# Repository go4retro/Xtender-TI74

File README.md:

# TI-74 Cartridge Port Extender

## Introduction

Basic port extender

## Requirements

- TI-74

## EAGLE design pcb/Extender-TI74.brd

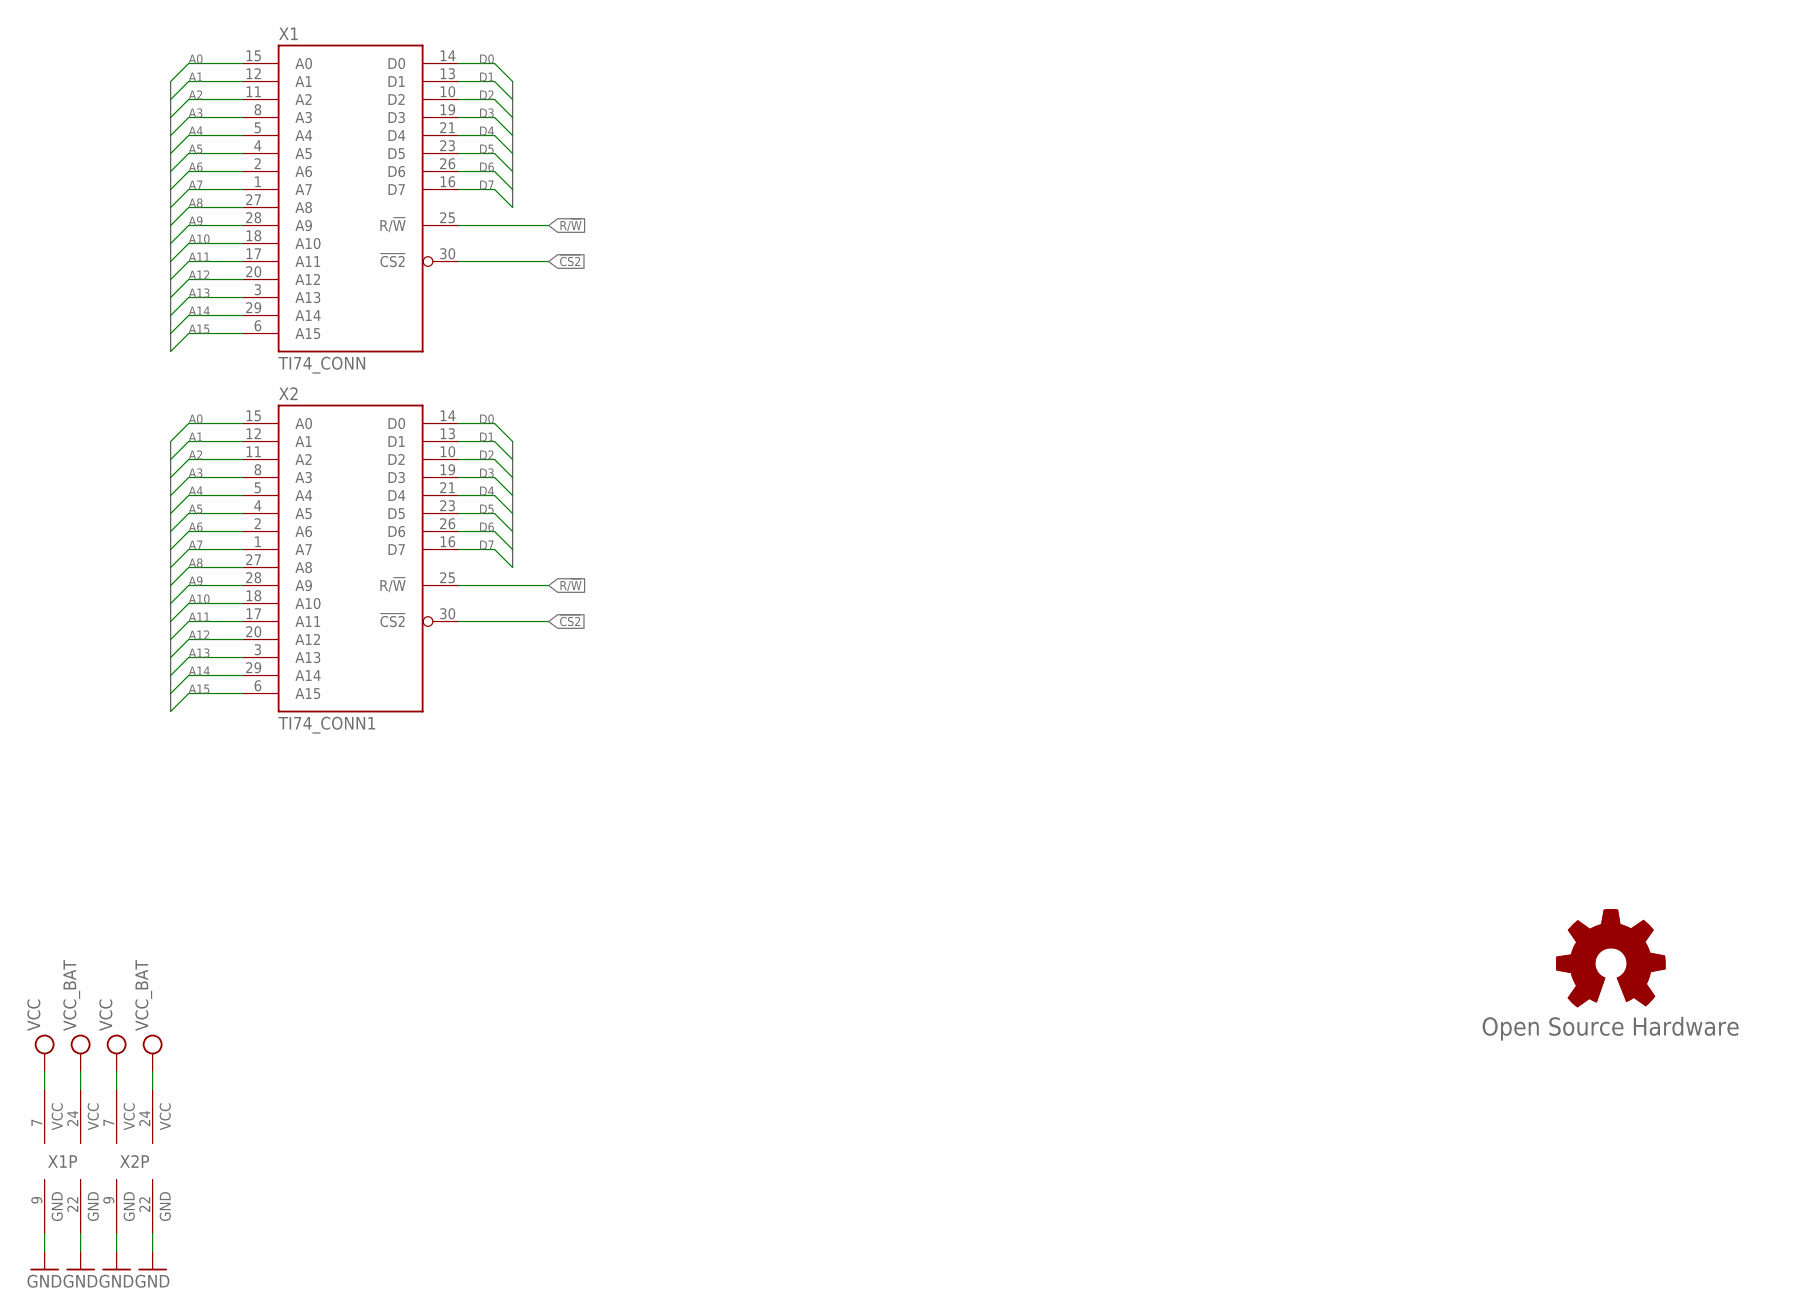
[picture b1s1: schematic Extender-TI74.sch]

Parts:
GOLD_ORB_SM1: Open Source Hardware; OSHW_5MM
X1: TI74_CONN; FE050-15-2SHORT
X2: TI74_CONN1; MA050-15-2

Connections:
!CS2: X1.30 (!CS2), X2.30 (!CS2)
A0: X1.15 (A0), X2.15 (A0)
A1: X1.12 (A1), X2.12 (A1)
A2: X1.11 (A2), X2.11 (A2)
A3: X1.8 (A3), X2.8 (A3)
A4: X1.5 (A4), X2.5 (A4)
A5: X1.4 (A5), X2.4 (A5)
A6: X1.2 (A6), X2.2 (A6)
A7: X1.1 (A7), X2.1 (A7)
A8: X1.27 (A8), X2.27 (A8)
A9: X1.28 (A9), X2.28 (A9)
A10: X1.18 (A10), X2.18 (A10)
A11: X1.17 (A11), X2.17 (A11)
A12: X1.20 (A12), X2.20 (A12)
A13: X1.3 (A13), X2.3 (A13)
A14: X1.29 (A14), X2.29 (A14)
A15: X1.6 (A15), X2.6 (A15)
D0: X1.14 (D0), X2.14 (D0)
D1: X1.13 (D1), X2.13 (D1)
D2: X1.10 (D2), X2.10 (D2)
D3: X1.19 (D3), X2.19 (D3)
D4: X1.21 (D4), X2.21 (D4)
D5: X1.23 (D5), X2.23 (D5)
D6: X1.26 (D6), X2.26 (D6)
D7: X1.16 (D7), X2.16 (D7)
GND: X1.9 (GND), X1.22 (GND), X2.9 (GND), X2.22 (GND)
R/!W: X1.25 (R/!W), X2.25 (R/!W)
VCC: X1.7 (VCC), X2.7 (VCC)
VCCBAT: X1.24 (VCC_RAM), X2.24 (VCC_RAM)

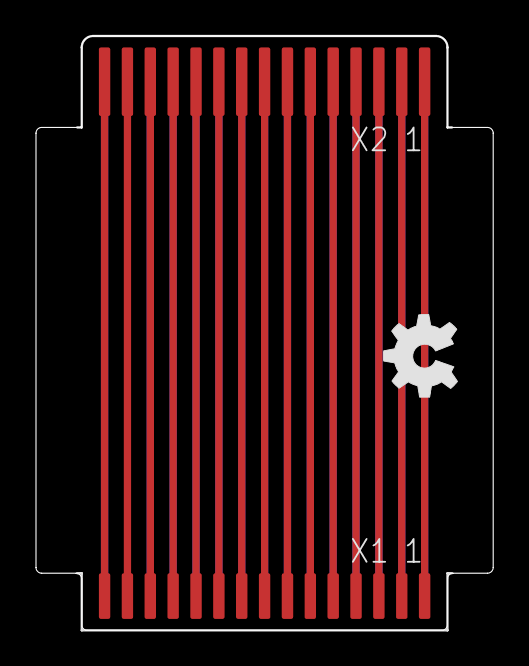
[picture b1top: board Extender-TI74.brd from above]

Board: 2 copper layers, 25.4 x 33.0 mm, 3 parts (0 on the bottom side), 29 nets.
